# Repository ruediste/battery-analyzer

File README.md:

# battery-analyzer
Open Source battery analyzer

# Resistor Matching
When building your channel boards, make sure to match the resistors. See `firmware/src/resistorMatcher.cpp` for details.

# Calibration

1. Calibrate Voltage: connect a PSU to the plus pole of the battery, apply about 4.2V. Measure the voltage and enter it.
1. Zero PWM:

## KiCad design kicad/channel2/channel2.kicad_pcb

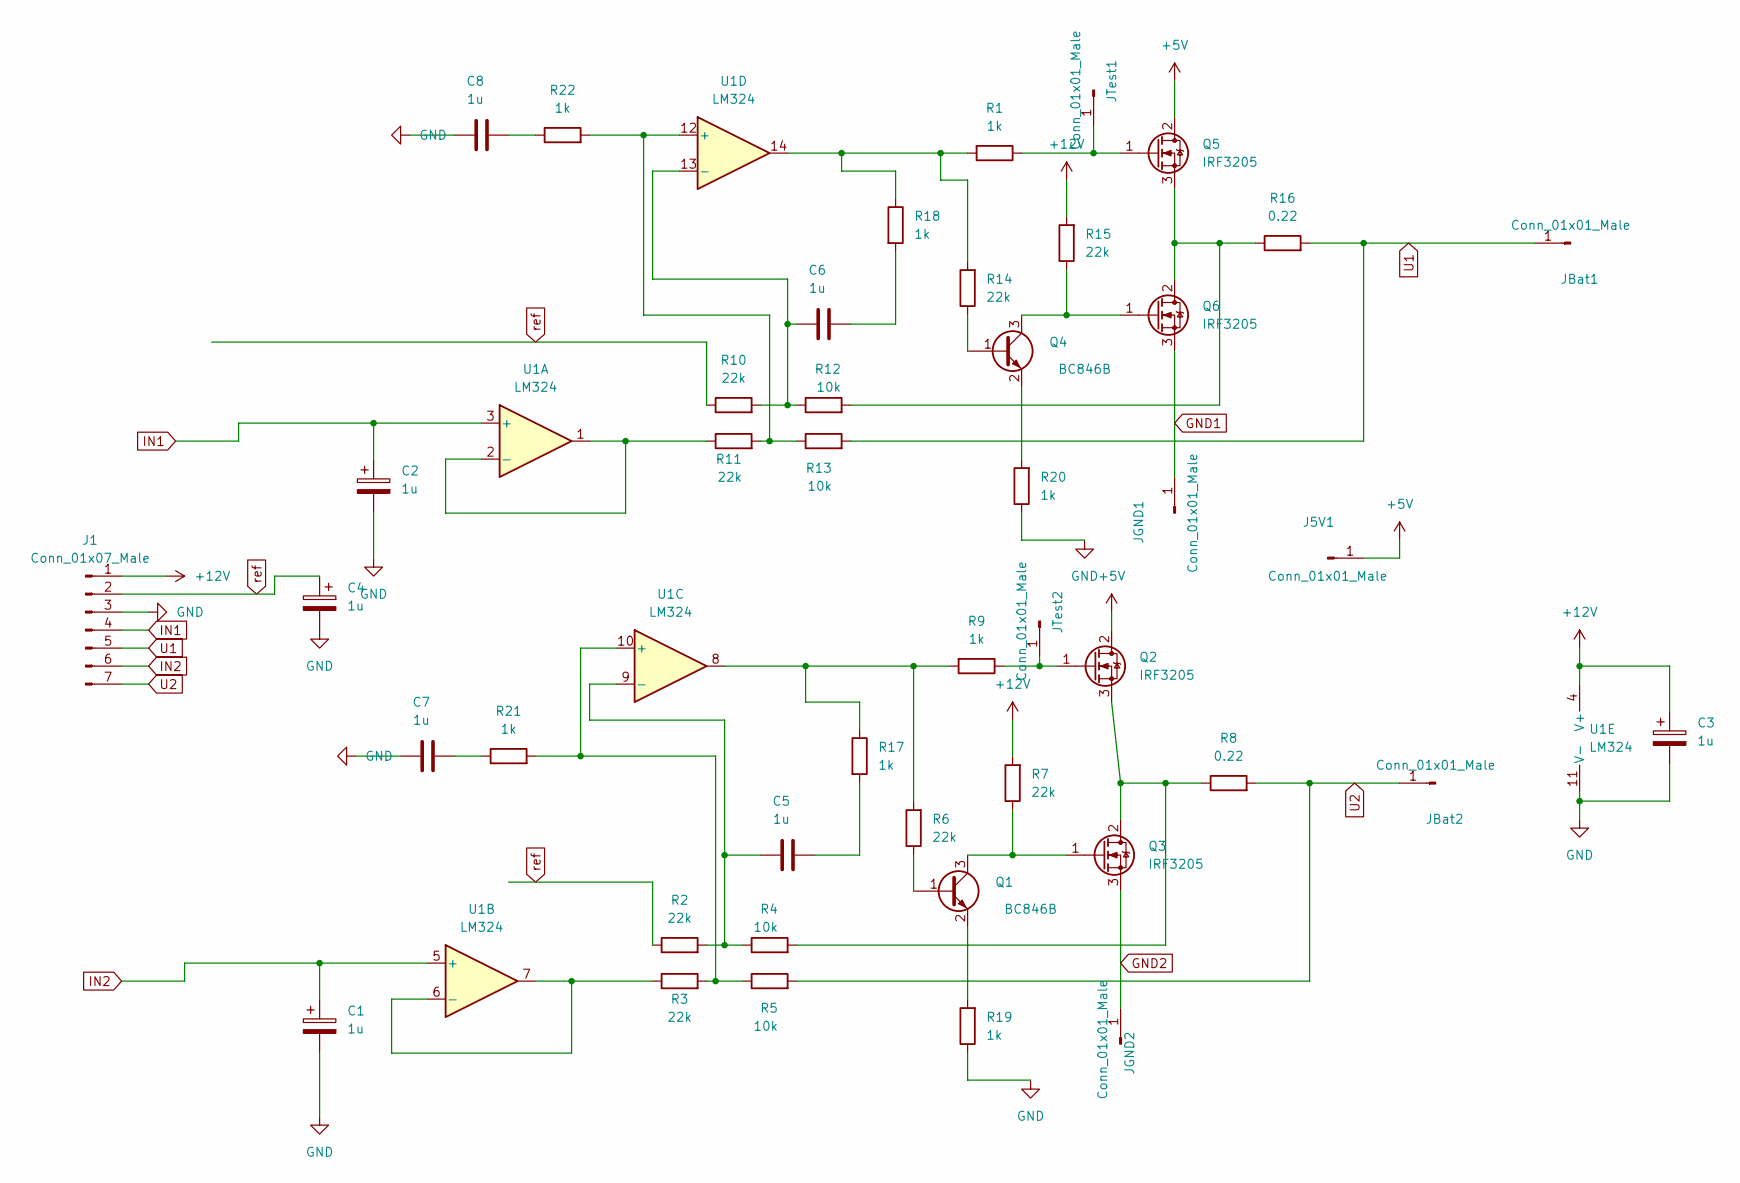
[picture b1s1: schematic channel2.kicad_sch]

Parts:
C1, C2, C3, C4, C5, C6, C7, C8: 1u; C_0603_1608Metric
J1: Conn_01x07_Male; PinHeader_1x07_P2.54mm_Vertical
J5V1: Conn_01x01_Male; PowerPad
JBat1, JBat2: Conn_01x01_Male; PowerPad
JGND1, JGND2: Conn_01x01_Male; PowerPad
JTest1, JTest2: Conn_01x01_Male; PinHeader_1x01_P2.54mm_Vertical
Q1, Q4: BC846B; SOT-23
Q2, Q3, Q5, Q6: IRF3205; TO-220-3_Vertical
R1, R9, R17, R18, R19, R20, R21, R22: 1k; R_1206_3216Metric
R2, R3, R6, R7, R10, R11, R14, R15: 22k; R_1206_3216Metric
R4, R5, R12, R13: 10k; R_1206_3216Metric
R8, R16: 0.22; R_Axial_DIN0617_L17.0mm_D6.0mm_P25.40mm_Horizontal
U1: LM324; SOIC-14_3.9x8.7mm_P1.27mm

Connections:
+5V: J5V1.1, Q2.2 (D), Q5.2 (D)
+12V: C3.1, J1.1, R7.2, R15.2, U1.4 (V+)
GND: C1.2, C2.2, C3.2, C4.2, C7.1, C8.1, J1.3, R19.1, R20.1, U1.11 (V-)
GND1: JGND1.1, Q6.3 (S)
GND2: JGND2.1, Q3.3 (S)
IN1: C2.1, J1.4, U1.3 (+)
IN2: C1.1, J1.6, U1.5 (+)
unnamed: C5.1, R2.2, R4.1, U1.9 (-)
unnamed: C5.2, R17.2
unnamed: C6.1, R10.2, R12.1, U1.13 (-)
unnamed: C6.2, R18.2
unnamed: C7.2, R21.1
unnamed: C8.2, R22.1
unnamed: JTest1.1, Q5.1 (G), R1.1
unnamed: JTest2.1, Q2.1 (G), R9.1
unnamed: Q1.1 (B), R6.1
unnamed: Q1.2 (E), R19.2
unnamed: Q1.3 (C), Q3.1 (G), R7.1
unnamed: Q2.3 (S), Q3.2 (D), R4.2, R8.1
unnamed: Q4.1 (B), R14.1
unnamed: Q4.2 (E), R20.2
unnamed: Q4.3 (C), Q6.1 (G), R15.1
unnamed: Q5.3 (S), Q6.2 (D), R12.2, R16.1
unnamed: R1.2, R14.2, R18.1, U1.14
unnamed: R3.1, U1.6 (-), U1.7
unnamed: R11.1, U1.1, U1.2 (-)
unnamed: R11.2, R13.1, R22.2, U1.12 (+)
unnamed: R6.2, R9.2, R17.1, U1.8
unnamed: R3.2, R5.1, R21.2, U1.10 (+)
U1: J1.5, JBat1.1, R13.2, R16.2
U2: J1.7, JBat2.1, R5.2, R8.2
ref: C4.1, J1.2, R2.1, R10.1

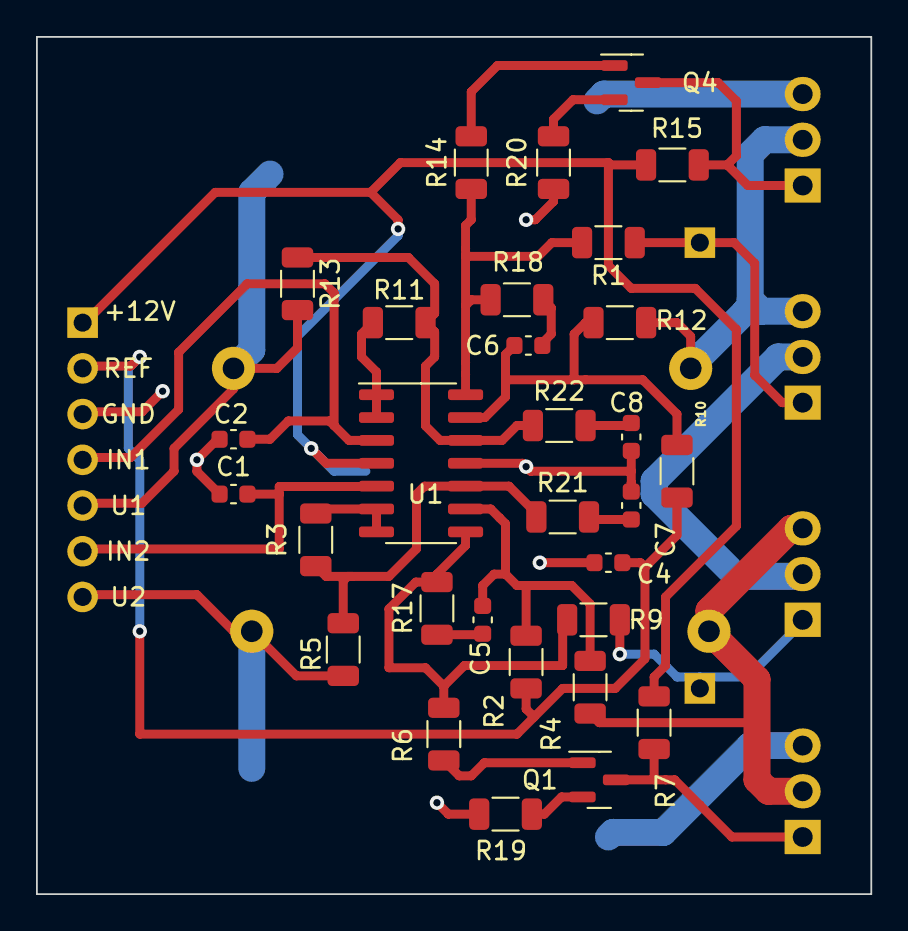
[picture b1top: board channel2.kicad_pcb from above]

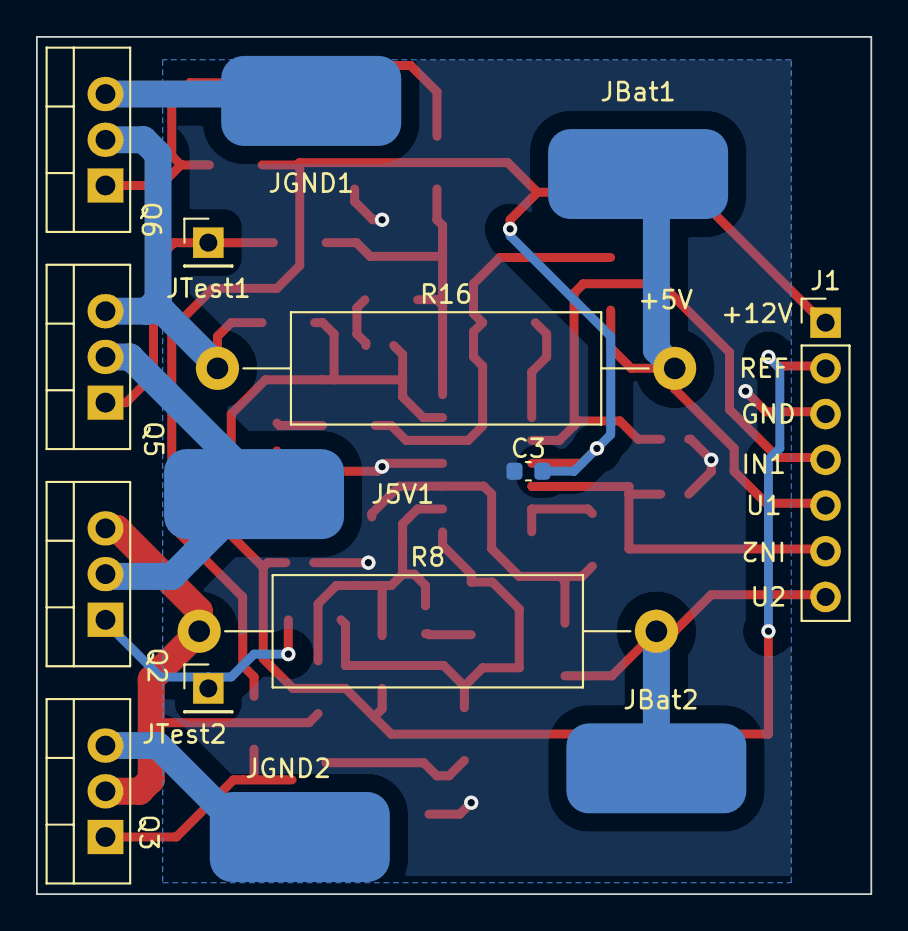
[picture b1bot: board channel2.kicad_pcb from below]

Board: 2 copper layers, 46.4 x 47.6 mm, 45 parts (15 on the bottom side), 32 nets.

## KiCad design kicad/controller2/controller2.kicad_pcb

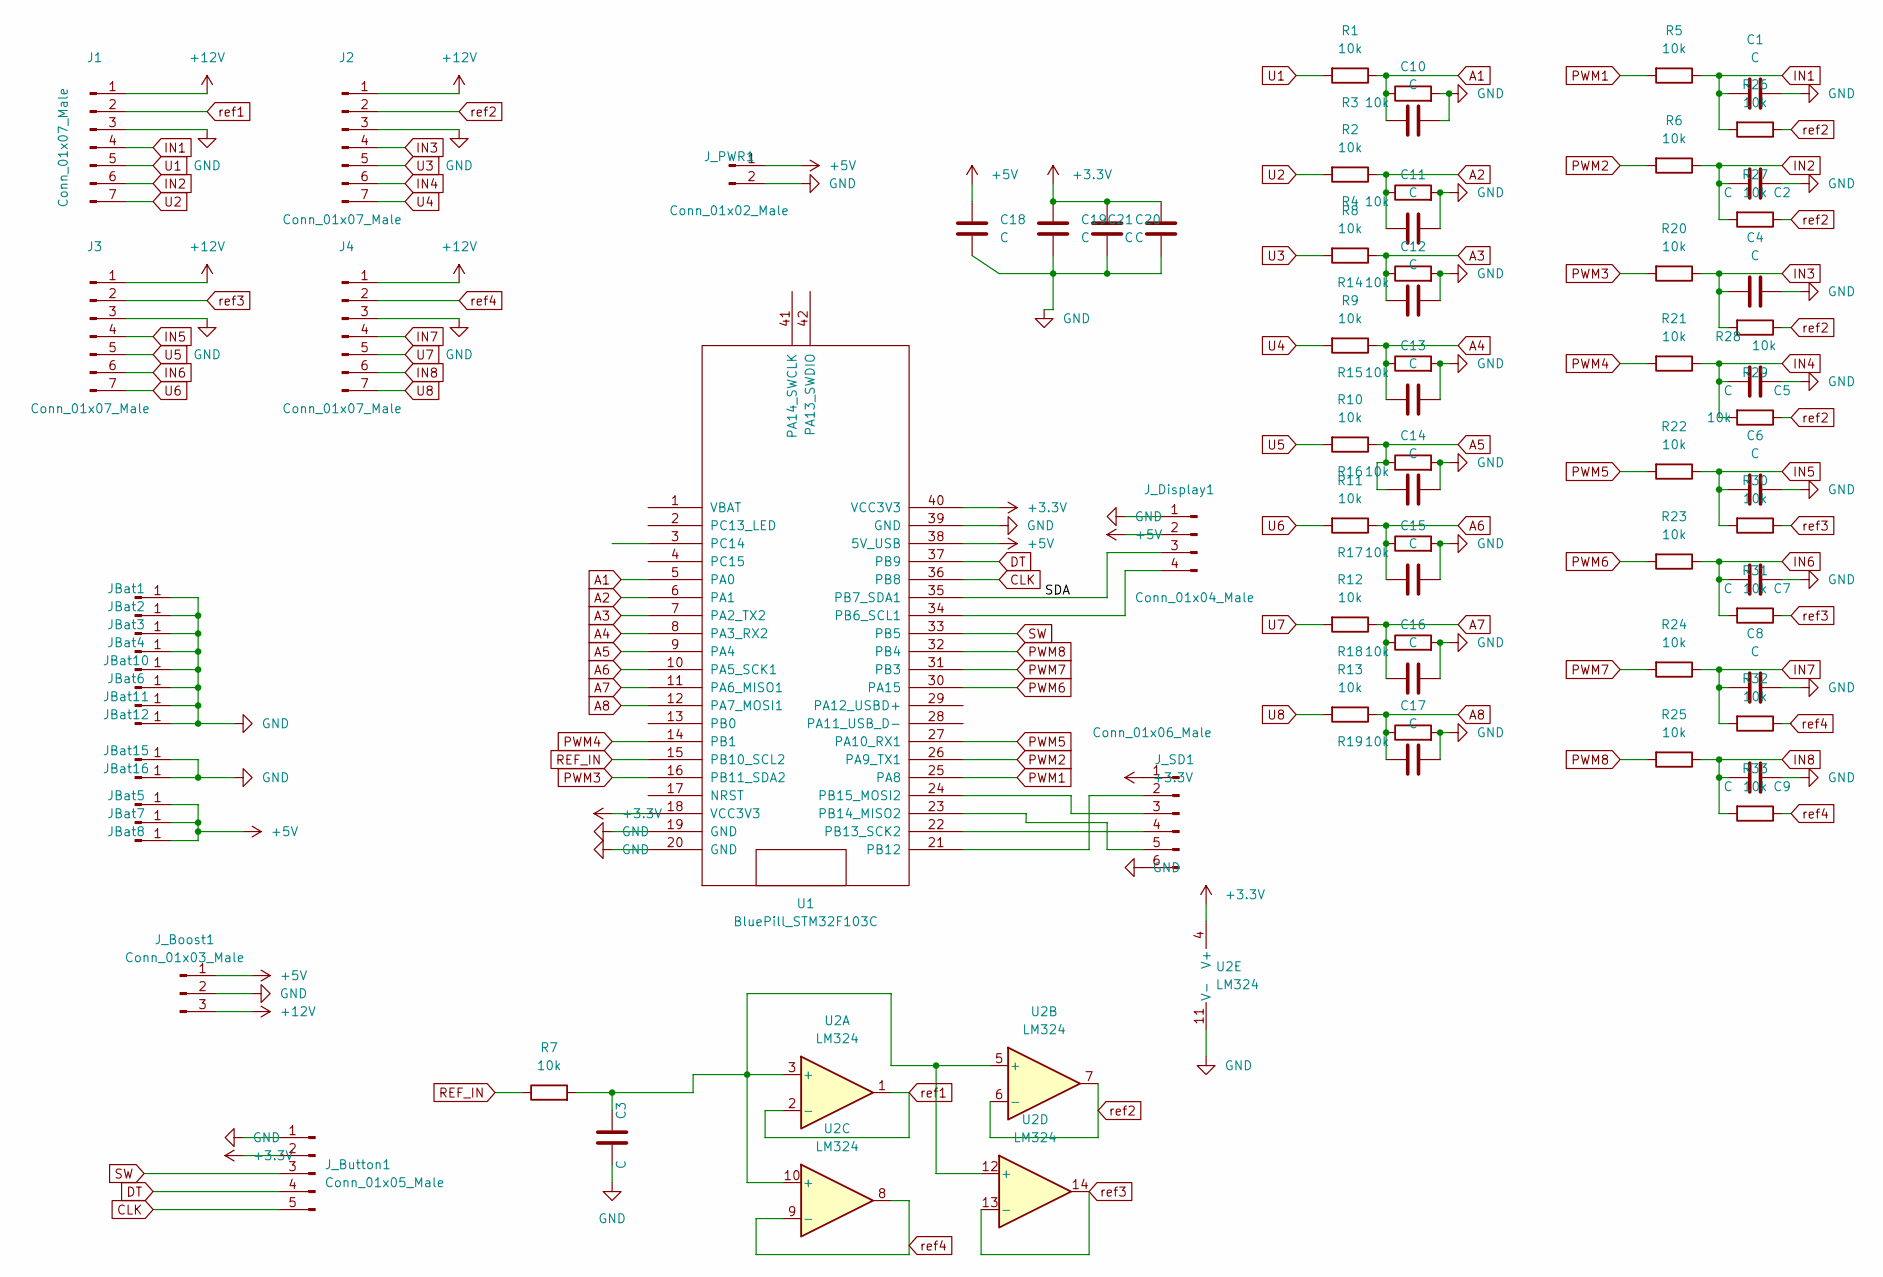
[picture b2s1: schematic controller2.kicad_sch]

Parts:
C1, C2, C3, C4, C5, C6, C7, C8, C9, C10, C11, C12, C13, C14, C15, C16, C17, C18, C19, C20, C21: C; C_0805_2012Metric
J1, J2, J3, J4: Conn_01x07_Male; PinHeader_1x07_P2.54mm_Vertical
JBat1, JBat2, JBat3, JBat4, JBat5, JBat6, JBat7, JBat8, JBat10, JBat11, JBat12, JBat15, JBat16: Conn_01x01_Male; PowerPin
J_Boost1: Conn_01x03_Male; PinHeader_1x03_P2.54mm_Vertical
J_Button1: Conn_01x05_Male; PinHeader_1x05_P2.54mm_Vertical
J_Display1: Conn_01x04_Male; PinHeader_1x04_P2.54mm_Vertical
J_PWR1: Conn_01x02_Male; PinHeader_1x02_P2.54mm_Vertical
J_SD1: Conn_01x06_Male; SD_Card_reader
R1, R2, R3, R4, R5, R6, R7, R8, R9, R10, R11, R12, R13, R14, R15, R16, R17, R18, R19, R20, R21, R22, R23, R24, R25, R26, R27, R28, R29, R30, R31, R32, R33: 10k; R_1206_3216Metric
U1: BluePill_STM32F103C; BluePill
U2: LM324; SOIC-14_3.9x8.7mm_P1.27mm

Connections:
+3.3V: C19.2, C20.2, C21.2, J_Button1.2, J_SD1.1, U1.18 (VCC3V3), U1.40 (VCC3V3), U2.4 (V+)
+5V: C18.2, JBat5.1, JBat7.1, JBat8.1, J_Boost1.1, J_Display1.2, J_PWR1.1, U1.38 (5V_USB)
+12V: J1.1, J2.1, J3.1, J4.1, J_Boost1.3
/SDA: J_Display1.3, U1.35 (PB7_SDA1)
A1: C10.1, R1.1, R3.1, U1.5 (PA0)
A2: C11.1, R2.1, R4.1, U1.6 (PA1)
A3: C12.1, R8.1, R14.1, U1.7 (PA2_TX2)
A4: C13.1, R9.1, R15.1, U1.8 (PA3_RX2)
A5: C14.1, R10.1, R16.1, U1.9 (PA4)
A6: C15.1, R11.1, R17.1, U1.10 (PA5_SCK1)
A7: C16.1, R12.1, R18.1, U1.11 (PA6_MISO1)
A8: C17.1, R13.1, R19.1, U1.12 (PA7_MOSI1)
CLK: J_Button1.5, U1.36 (PB8)
DT: J_Button1.4, U1.37 (PB9)
GND: C1.2, C2.2, C3.1, C4.2, C5.2, C6.2, C7.2, C8.2, C9.2, C10.2, C11.2, C12.2, C13.2, C14.2, C15.2, C16.2, C17.2, C18.1, C19.1, C20.1, C21.1, J1.3, J2.3, J3.3, J4.3, JBat1.1, JBat2.1, JBat3.1, JBat4.1, JBat6.1, JBat10.1, JBat11.1, JBat12.1, JBat15.1, JBat16.1, J_Boost1.2, J_Button1.1, J_Display1.1, J_PWR1.2, J_SD1.6, R3.2, R4.2, R14.2, R15.2, R16.2, R17.2, R18.2, R19.2, U1.19 (GND), U1.20 (GND), U1.39 (GND), U2.11 (V-)
IN1: C1.1, J1.4, R5.1, R26.2
IN2: C2.1, J1.6, R6.1, R27.2
IN3: C4.1, J2.4, R20.1, R28.2
IN4: C5.1, J2.6, R21.1, R29.2
IN5: C6.1, J3.4, R22.1, R30.2
IN6: C7.1, J3.6, R23.1, R31.2
IN7: C8.1, J4.4, R24.1, R32.2
IN8: C9.1, J4.6, R25.1, R33.2
unnamed: C3.2, R7.2, U2.3 (+), U2.5 (+), U2.10 (+), U2.12 (+)
unnamed: J_Display1.4, U1.34 (PB6_SCL1)
unnamed: J_SD1.2, U1.21 (PB12)
unnamed: J_SD1.3, U1.24 (PB15_MOSI2)
unnamed: J_SD1.4, U1.22 (PB13_SCK2)
unnamed: J_SD1.5, U1.23 (PB14_MISO2)
PWM1: R5.2, U1.25 (PA8)
PWM2: R6.2, U1.26 (PA9_TX1)
PWM3: R20.2, U1.16 (PB11_SDA2)
PWM4: R21.2, U1.14 (PB1)
PWM5: R22.2, U1.27 (PA10_RX1)
PWM6: R23.2, U1.30 (PA15)
PWM7: R24.2, U1.31 (PB3)
PWM8: R25.2, U1.32 (PB4)
REF_IN: R7.1, U1.15 (PB10_SCL2)
SW: J_Button1.3, U1.33 (PB5)
U1: J1.5, R1.2
U2: J1.7, R2.2
U3: J2.5, R8.2
U4: J2.7, R9.2
U5: J3.5, R10.2
U6: J3.7, R11.2
U7: J4.5, R12.2
U8: J4.7, R13.2
ref1: J1.2, U2.1, U2.2 (-)
ref2: J2.2, R26.1, R27.1, R28.1, R29.1, U2.6 (-), U2.7
ref3: J3.2, R30.1, R31.1, U2.13 (-), U2.14
ref4: J4.2, R32.1, R33.1, U2.8, U2.9 (-)

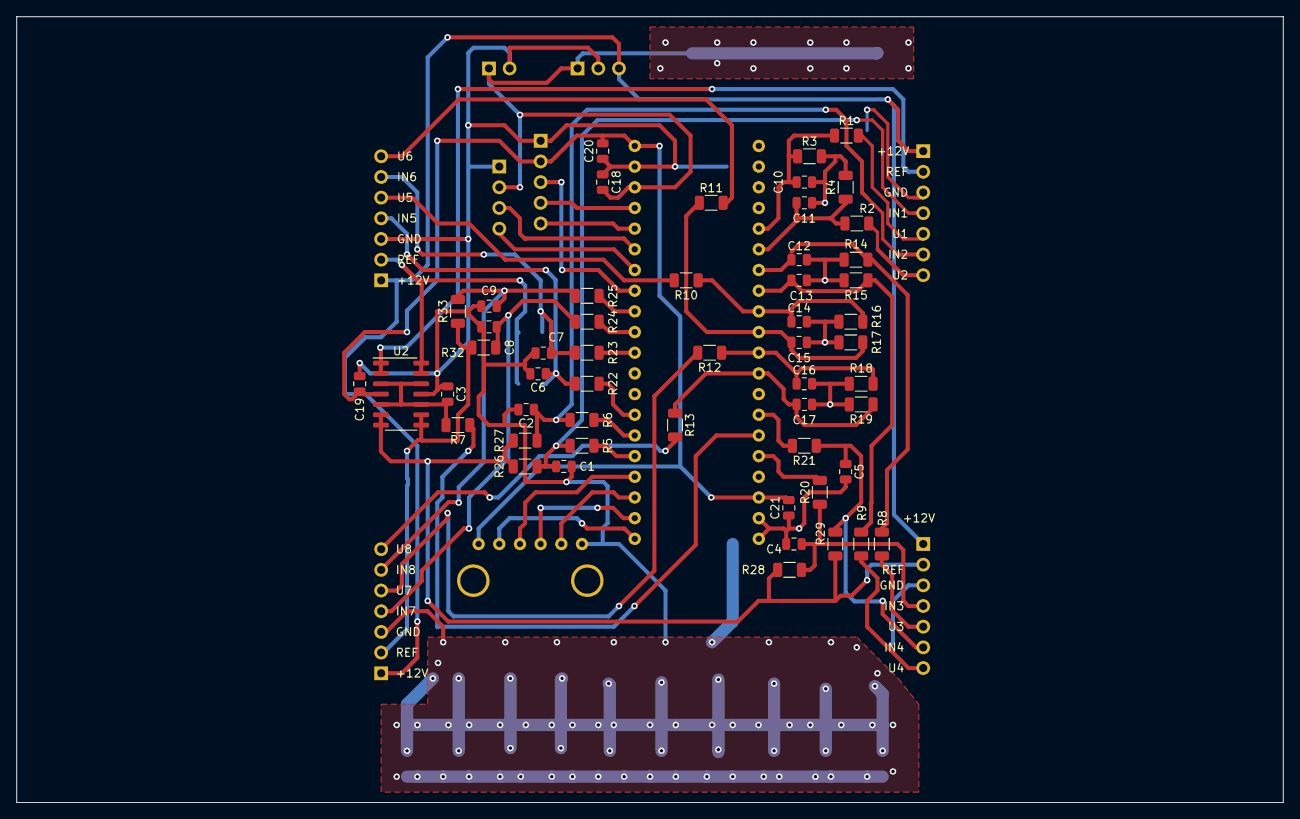
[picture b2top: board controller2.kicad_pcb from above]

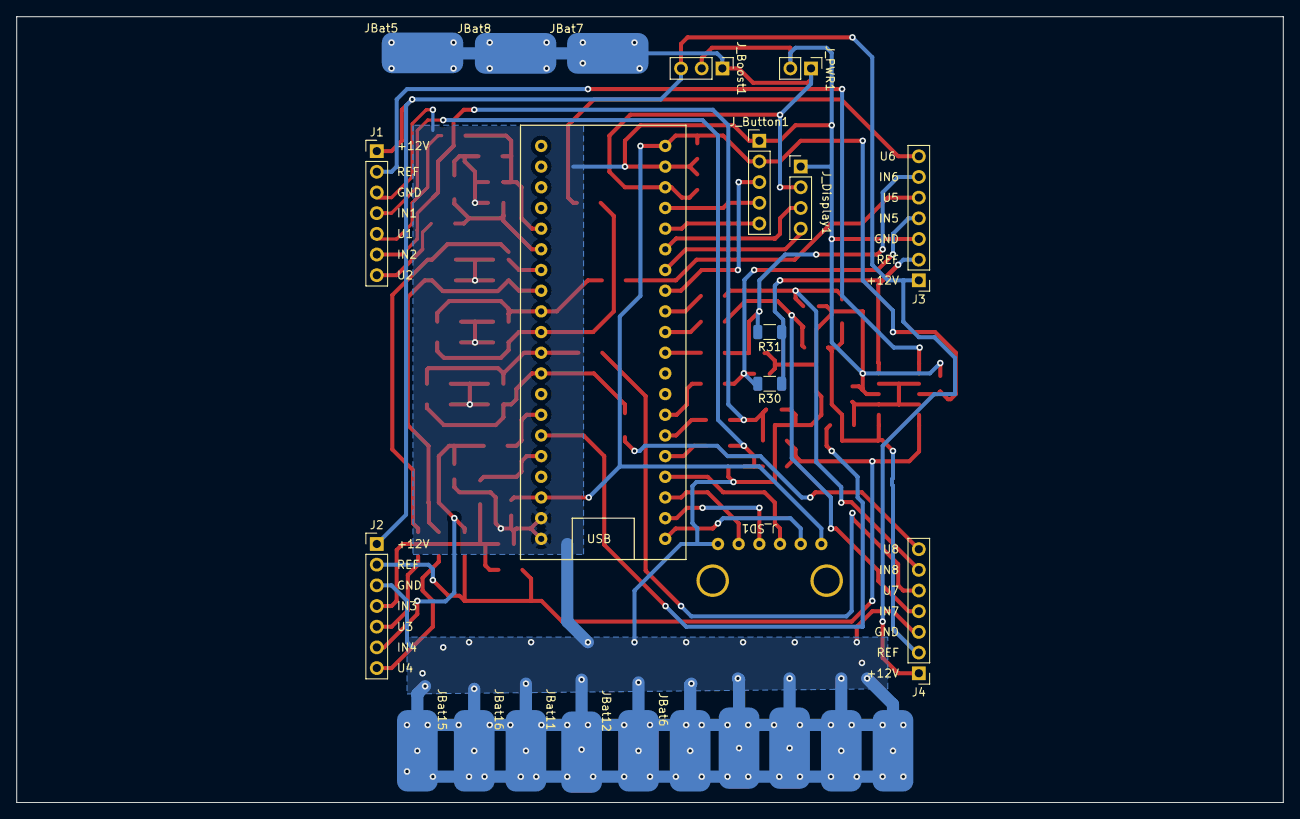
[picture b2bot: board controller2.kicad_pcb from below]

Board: 2 copper layers, 155.6 x 96.5 mm, 78 parts (25 on the bottom side), 51 nets.

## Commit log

2022-07-10 add display
2022-07-10 get menu working
2022-07-12 get basic functionality working
2022-08-10 switch to ncurses
2022-08-13 fix ncurses boxes
2022-08-13 switch to cc controlled hardware
2022-08-14 add config
2022-08-18 work on configuration
2022-08-21 improve power control
2022-08-22 fix build
2022-08-28 work on control and menu
2022-08-29 add holder scad
2022-08-31 work on holder
2022-09-01 add direct PWM mode
2022-09-10 add statistics
2022-09-10 add kicad
2022-09-12 add connectionResistance
2022-09-13 work on kicad
2022-09-16 rework PINS, get SD Card working
2022-09-23 fix flash, fix frequency compensation
2022-09-23 add qucs
2022-09-27 add resistor matching
2022-09-29 move mosfets
2022-10-01 sd logging
2022-10-02 fix calculation bug, EEPROM reset confirmation question
2022-10-02 implement Test charger mode
2022-10-03 minory diplay improvements
2022-10-08 work on pulse charge/discharge, combined board
2022-10-08 finish limit extension
2022-10-08 remove limit extension, fix pre discharge bug
2022-10-09 improve statistics
2022-10-09 small bugfixes
2022-10-15 fix resistor values around transistor
2022-10-18 minor schematic cleanups, improve opamp compensation
2022-12-04 cleanup
